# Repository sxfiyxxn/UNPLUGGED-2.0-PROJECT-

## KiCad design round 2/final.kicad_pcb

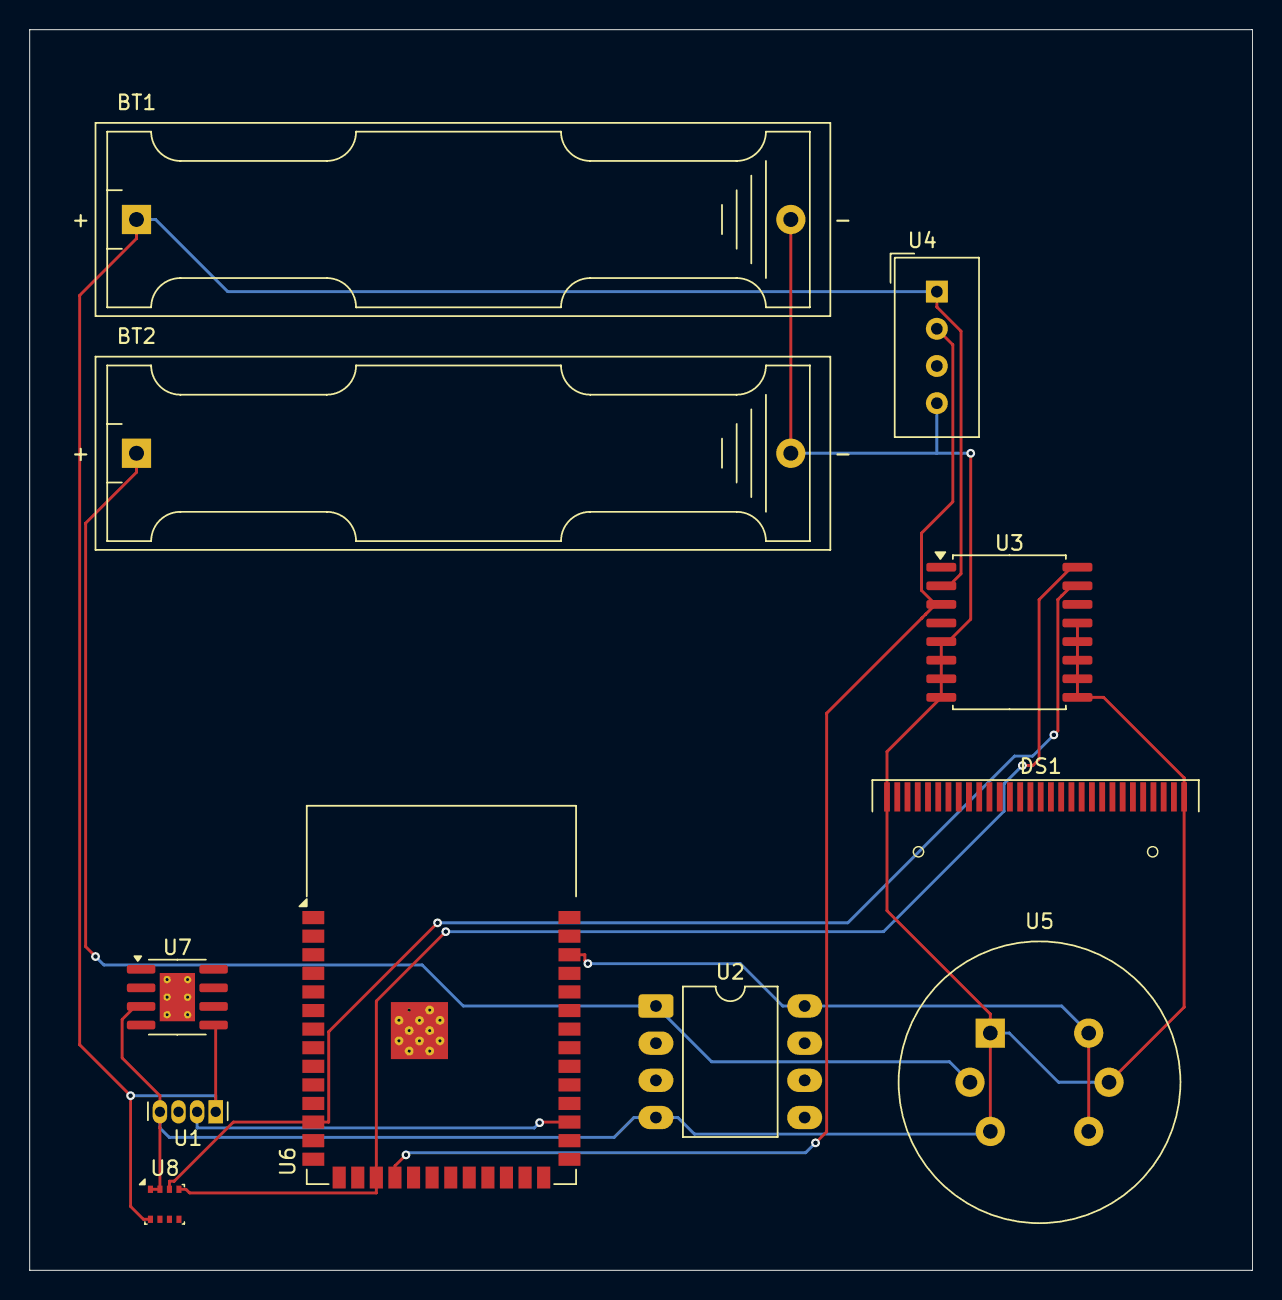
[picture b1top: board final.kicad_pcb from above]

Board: 2 copper layers, 83.5 x 84.8 mm, 11 parts (0 on the bottom side), 8 nets.

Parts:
BT1: 3.3; BatteryHolder_Keystone_2466_1xAAA
BT2: 5; BatteryHolder_Keystone_2466_1xAAA
DS1: OLED-128O064D
U1: A1363xKTTN-1; Allegro_SIP-4
U2: MAX471; DIP-8_W10.16mm_LongPads
U3: DS3231M; SOIC-16W_7.5x10.3mm_P1.27mm
U4: DHT11; Aosong_DHT11_5.5x12.0_P2.54mm
U5: MQ-6
U6: ESP32-S3-WROOM-1
U7: TP4056-42-ESOP8; SOIC-8-1EP_3.9x4.9mm_P1.27mm_EP2.41x3.3mm_ThermalVias
U8: BME280; Bosch_LGA-8_2.5x2.5mm_P0.65mm_ClockwisePinNumbering

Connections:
GND: BT1.2 (-), BT2.2 (-), DS1.1 (GND), DS1.30 (GND), U1.4 (GND), U2.4 (GND), U3.5 (GND), U3.6 (GND), U3.7 (GND), U3.8 (GND), U3.9 (GND), U3.10 (GND), U3.11 (GND), U3.12 (GND), U3.13 (GND), U4.4 (GND), U5.1 (B1), U5.3 (B2), U5.5 (VH-), U7.3 (GND), U8.1 (GND), U8.2 (CSB)
unnamed: BT1.1 (+), U1.1 (VCC), U3.2 (VCC), U4.1 (VDD), U7.5 (BAT), U8.8 (VDD)
unnamed: BT2.1 (+), U2.1 (SHDN), U5.2 (VH+)
unnamed: U1.2 (VOUT), U6.29 (IO36)
unnamed: U2.8 (OUT), U5.4 (A2), U5.6 (A1), U6.38 (IO2)
unnamed: U3.16 (SCL), U6.17 (IO9), U8.4 (SCK)
unnamed: U3.15 (SDA), U6.12 (IO8), U8.3 (SDI)
unnamed: U3.3 (~INT/SQW), U4.2 (DATA), U6.18 (IO10)
